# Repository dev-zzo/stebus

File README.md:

# IEEE 1000 / STEBus designs

This repository contains hardware designs based on the IEEE 1000 aka STE bus.

# Designs included

* S68k8: MC68008FN CPU board + bus arbiter
* STEP1: I/O prototyping board

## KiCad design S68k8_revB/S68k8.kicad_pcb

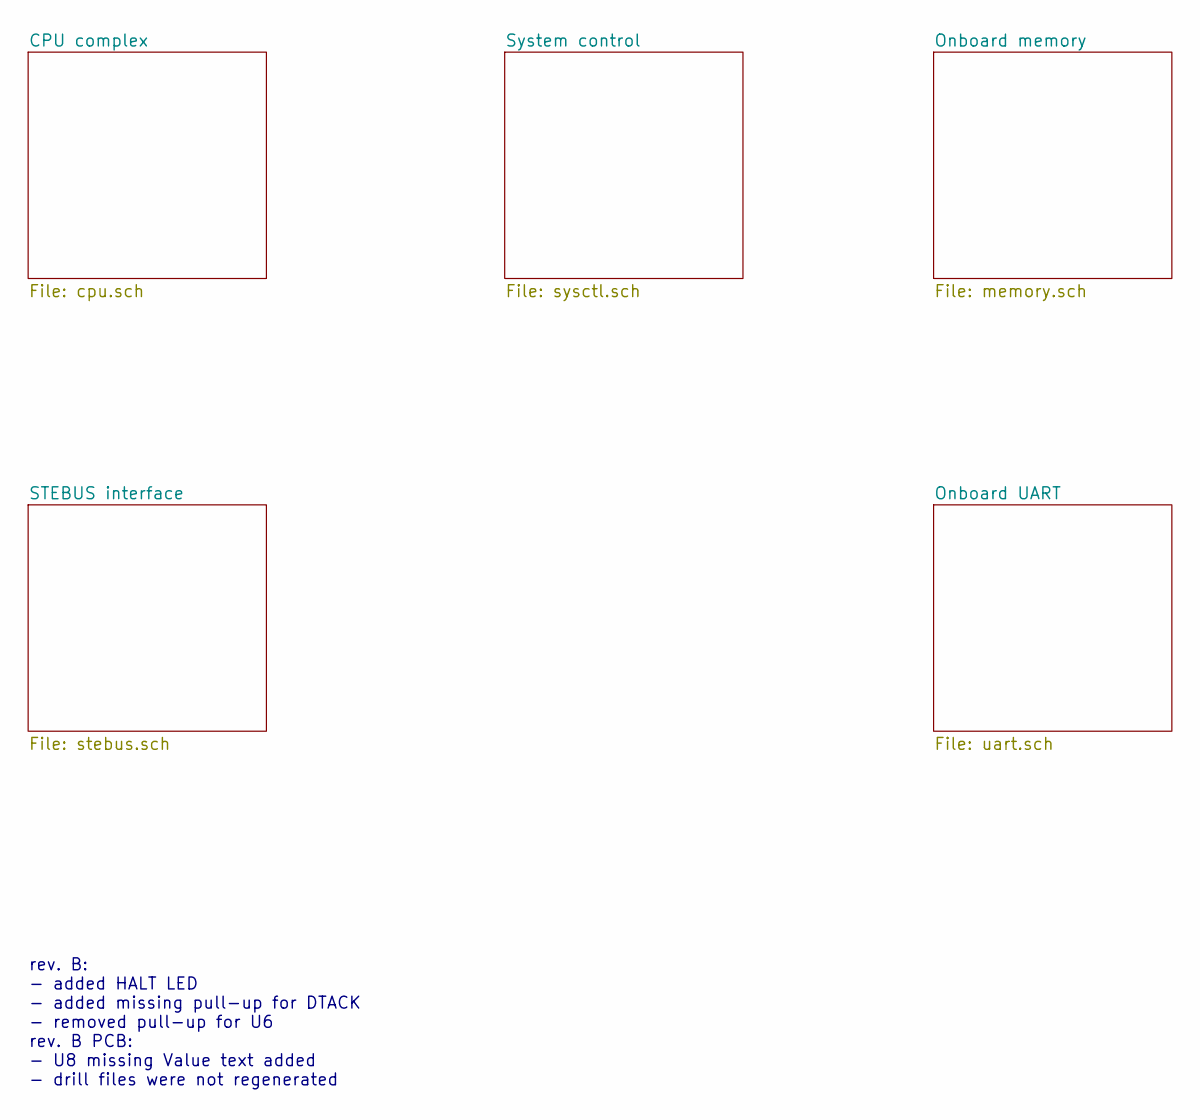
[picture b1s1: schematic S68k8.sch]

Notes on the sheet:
rev. B: - added HALT LED - added missing pull-up for DTACK - removed pull-up for U6 rev. B PCB: - U8 missing Value text added - drill files were not regenerated

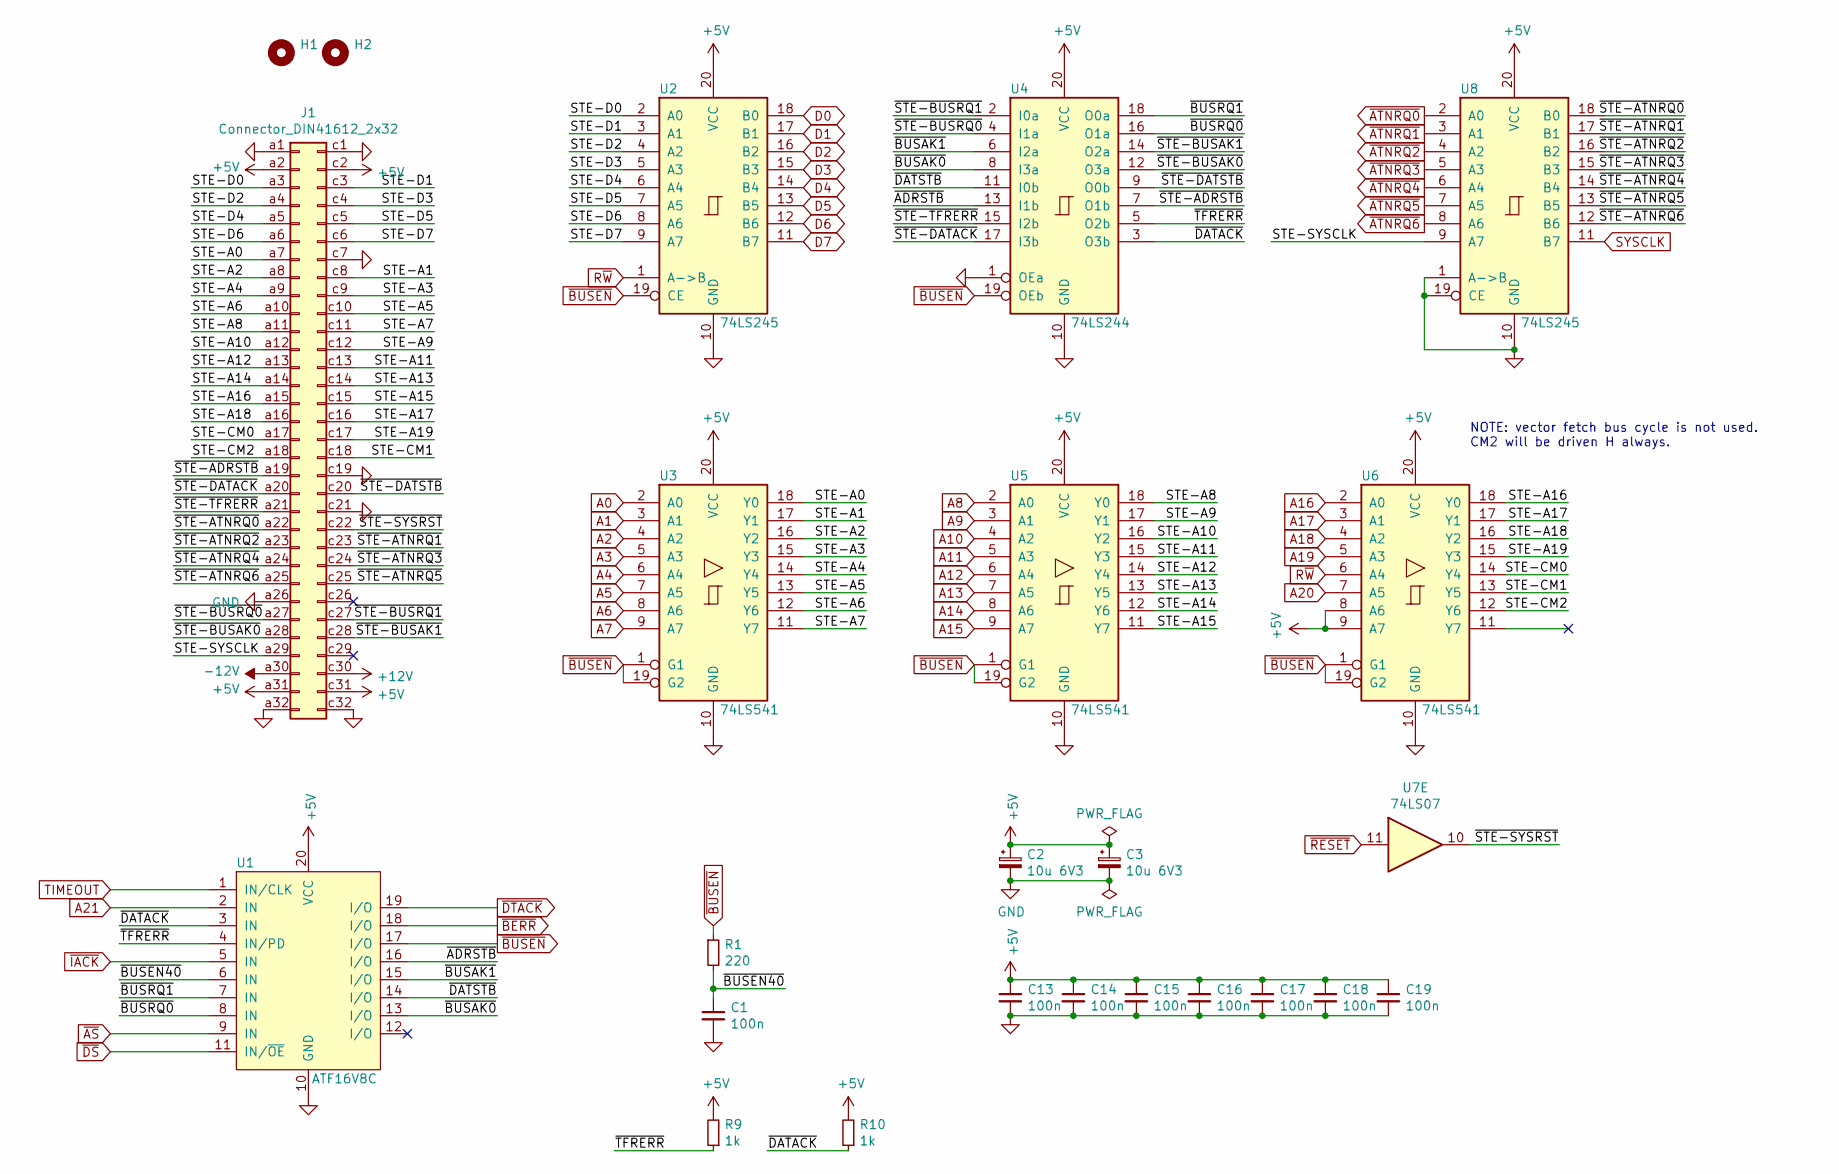
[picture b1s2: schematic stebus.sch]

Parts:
C1, C13, C14, C15, C16, C17, C18, C19: 100n; C_Rect_L7.0mm_W2.0mm_P5.00mm
C2, C3: 10u 6V3; CP_Radial_Tantal_D4.5mm_P5.00mm
H1, H2: MountingHole; MountingHole_2.7mm_M2.5
J1: Connector_DIN41612_2x32; DIN41612_C_2x32_Male_Horizontal_THT
R1: 220; R_Axial_DIN0204_L3.6mm_D1.6mm_P7.62mm_Horizontal
R9, R10: 1k; R_Axial_DIN0204_L3.6mm_D1.6mm_P7.62mm_Horizontal
U1: ATF16V8C; DIP-20_W7.62mm
U2, U8: 74LS245; DIP-20_W7.62mm
U3, U5, U6: 74LS541; DIP-20_W7.62mm
U4: 74LS244; DIP-20_W7.62mm
U7: 74LS07; DIP-14_W7.62mm

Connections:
+5V: C2.1, C3.1, C13.1, C14.1, C15.1, C16.1, C17.1, C18.1, C19.1, J1.a2, J1.a31, J1.c2, J1.c31, R9.2, R10.2, U1.20 (VCC), U2.20 (VCC), U3.20 (VCC), U4.20 (VCC), U5.20 (VCC), U6.8 (A6), U6.9 (A7), U6.20 (VCC), U8.20 (VCC); also elsewhere on the board
+12V: J1.c30; also elsewhere on the board
-12V: J1.a30; also elsewhere on the board
/STEBUS interface/STE-A0: J1.a7, U3.18 (Y0)
/STEBUS interface/STE-A1: J1.c8, U3.17 (Y1)
/STEBUS interface/STE-A2: J1.a8, U3.16 (Y2)
/STEBUS interface/STE-A3: J1.c9, U3.15 (Y3)
/STEBUS interface/STE-A4: J1.a9, U3.14 (Y4)
/STEBUS interface/STE-A5: J1.c10, U3.13 (Y5)
/STEBUS interface/STE-A6: J1.a10, U3.12 (Y6)
/STEBUS interface/STE-A7: J1.c11, U3.11 (Y7)
/STEBUS interface/STE-A8: J1.a11, U5.18 (Y0)
/STEBUS interface/STE-A9: J1.c12, U5.17 (Y1)
/STEBUS interface/STE-A10: J1.a12, U5.16 (Y2)
/STEBUS interface/STE-A11: J1.c13, U5.15 (Y3)
/STEBUS interface/STE-A12: J1.a13, U5.14 (Y4)
/STEBUS interface/STE-A13: J1.c14, U5.13 (Y5)
/STEBUS interface/STE-A14: J1.a14, U5.12 (Y6)
/STEBUS interface/STE-A15: J1.c15, U5.11 (Y7)
/STEBUS interface/STE-A16: J1.a15, U6.18 (Y0)
/STEBUS interface/STE-A17: J1.c16, U6.17 (Y1)
/STEBUS interface/STE-A18: J1.a16, U6.16 (Y2)
/STEBUS interface/STE-A19: J1.c17, U6.15 (Y3)
/STEBUS interface/STE-CM0: J1.a17, U6.14 (Y4)
/STEBUS interface/STE-CM1: J1.c18, U6.13 (Y5)
/STEBUS interface/STE-CM2: J1.a18, U6.12 (Y6)
/STEBUS interface/STE-D0: J1.a3, U2.2 (A0)
/STEBUS interface/STE-D1: J1.c3, U2.3 (A1)
/STEBUS interface/STE-D2: J1.a4, U2.4 (A2)
/STEBUS interface/STE-D3: J1.c4, U2.5 (A3)
/STEBUS interface/STE-D4: J1.a5, U2.6 (A4)
/STEBUS interface/STE-D5: J1.c5, U2.7 (A5)
/STEBUS interface/STE-D6: J1.a6, U2.8 (A6)
/STEBUS interface/STE-D7: J1.c6, U2.9 (A7)
/STEBUS interface/STE-SYSCLK: J1.a29, U8.9 (A7)
/STEBUS interface/~ADRSTB: U1.16 (I/O), U4.13 (I1b)
/STEBUS interface/~BUSAK0: U1.13 (I/O), U4.8 (I3a)
/STEBUS interface/~BUSAK1: U1.15 (I/O), U4.6 (I2a)
/STEBUS interface/~BUSEN40: C1.1, R1.2, U1.6 (IN)
/STEBUS interface/~BUSRQ0: U1.8 (IN), U4.16 (O1a)
/STEBUS interface/~BUSRQ1: U1.7 (IN), U4.18 (O0a)
/STEBUS interface/~DATACK: R10.1, U1.3 (IN), U4.3 (O3b)
/STEBUS interface/~DATSTB: U1.14 (I/O), U4.11 (I0b)
/STEBUS interface/~STE-ADRSTB: J1.a19, U4.7 (O1b)
/STEBUS interface/~STE-ATNRQ0: J1.a22, U8.18 (B0)
/STEBUS interface/~STE-ATNRQ1: J1.c23, U8.17 (B1)
/STEBUS interface/~STE-ATNRQ2: J1.a23, U8.16 (B2)
/STEBUS interface/~STE-ATNRQ3: J1.c24, U8.15 (B3)
/STEBUS interface/~STE-ATNRQ4: J1.a24, U8.14 (B4)
/STEBUS interface/~STE-ATNRQ5: J1.c25, U8.13 (B5)
/STEBUS interface/~STE-ATNRQ6: J1.a25, U8.12 (B6)
/STEBUS interface/~STE-BUSAK0: J1.a28, U4.12 (O3a)
/STEBUS interface/~STE-BUSAK1: J1.c28, U4.14 (O2a)
/STEBUS interface/~STE-BUSRQ0: J1.a27, U4.4 (I1a)
/STEBUS interface/~STE-BUSRQ1: J1.c27, U4.2 (I0a)
/STEBUS interface/~STE-DATACK: J1.a20, U4.17 (I3b)
/STEBUS interface/~STE-DATSTB: J1.c20, U4.9 (O0b)
/STEBUS interface/~STE-SYSRST: J1.c22, U7.10
/STEBUS interface/~STE-TFRERR: J1.a21, U4.15 (I2b)
/STEBUS interface/~TFRERR: R9.1, U1.4 (IN/PD), U4.5 (O2b)
A0: U3.2 (A0); also elsewhere on the board
A1: U3.3 (A1); also elsewhere on the board
A2: U3.4 (A2); also elsewhere on the board
A3: U3.5 (A3); also elsewhere on the board
A4: U3.6 (A4); also elsewhere on the board
A5: U3.7 (A5); also elsewhere on the board
A6: U3.8 (A6); also elsewhere on the board
A7: U3.9 (A7); also elsewhere on the board
A8: U5.2 (A0); also elsewhere on the board
A9: U5.3 (A1); also elsewhere on the board
A10: U5.4 (A2); also elsewhere on the board
A11: U5.5 (A3); also elsewhere on the board
A12: U5.6 (A4); also elsewhere on the board
A13: U5.7 (A5); also elsewhere on the board
A14: U5.8 (A6); also elsewhere on the board
A15: U5.9 (A7); also elsewhere on the board
A16: U6.2 (A0); also elsewhere on the board
A17: U6.3 (A1); also elsewhere on the board
A18: U6.4 (A2); also elsewhere on the board
A19: U6.5 (A3); also elsewhere on the board
A20: U6.7 (A5); also elsewhere on the board
A21: U1.2 (IN); also elsewhere on the board
D0: U2.18 (B0); also elsewhere on the board
D1: U2.17 (B1); also elsewhere on the board
D2: U2.16 (B2); also elsewhere on the board
D3: U2.15 (B3); also elsewhere on the board
D4: U2.14 (B4); also elsewhere on the board
D5: U2.13 (B5); also elsewhere on the board
D6: U2.12 (B6); also elsewhere on the board
D7: U2.11 (B7); also elsewhere on the board
GND: C1.2, C2.2, C3.2, C13.2, C14.2, C15.2, C16.2, C17.2, C18.2, C19.2, J1.a1, J1.a26, J1.a32, J1.c1, J1.c7, J1.c19, J1.c21, J1.c32, U1.10 (GND), U2.10 (GND), U3.10 (GND), U4.1 (OEa), U4.10 (GND), U5.10 (GND), U6.10 (GND), U8.1 (A->B), U8.10 (GND), U8.19 (CE); also elsewhere on the board
R~W: U2.1 (A->B), U6.6 (A4); also elsewhere on the board
SYSCLK: U8.11 (B7); also elsewhere on the board
TIMEOUT: U1.1 (IN/CLK); also elsewhere on the board
~AS: U1.9 (IN); also elsewhere on the board
~ATNRQ0: U8.2 (A0); also elsewhere on the board
~ATNRQ1: U8.3 (A1); also elsewhere on the board
~ATNRQ2: U8.4 (A2); also elsewhere on the board
~ATNRQ3: U8.5 (A3); also elsewhere on the board
~ATNRQ4: U8.6 (A4); also elsewhere on the board
~ATNRQ5: U8.7 (A5); also elsewhere on the board
~ATNRQ6: U8.8 (A6); also elsewhere on the board
~BERR: U1.18 (I/O); also elsewhere on the board
~BUSEN: R1.1, U1.17 (I/O), U2.19 (CE), U3.1 (G1), U3.19 (G2), U4.19 (OEb), U5.1 (G1), U5.19 (G2), U6.1 (G1), U6.19 (G2); also elsewhere on the board
~DS: U1.11 (IN/~OE); also elsewhere on the board
~DTACK: U1.19 (I/O); also elsewhere on the board
~IACK: U1.5 (IN); also elsewhere on the board
~RESET: U7.11; also elsewhere on the board

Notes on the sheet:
NOTE: vector fetch bus cycle is not used. CM2 will be driven H always.

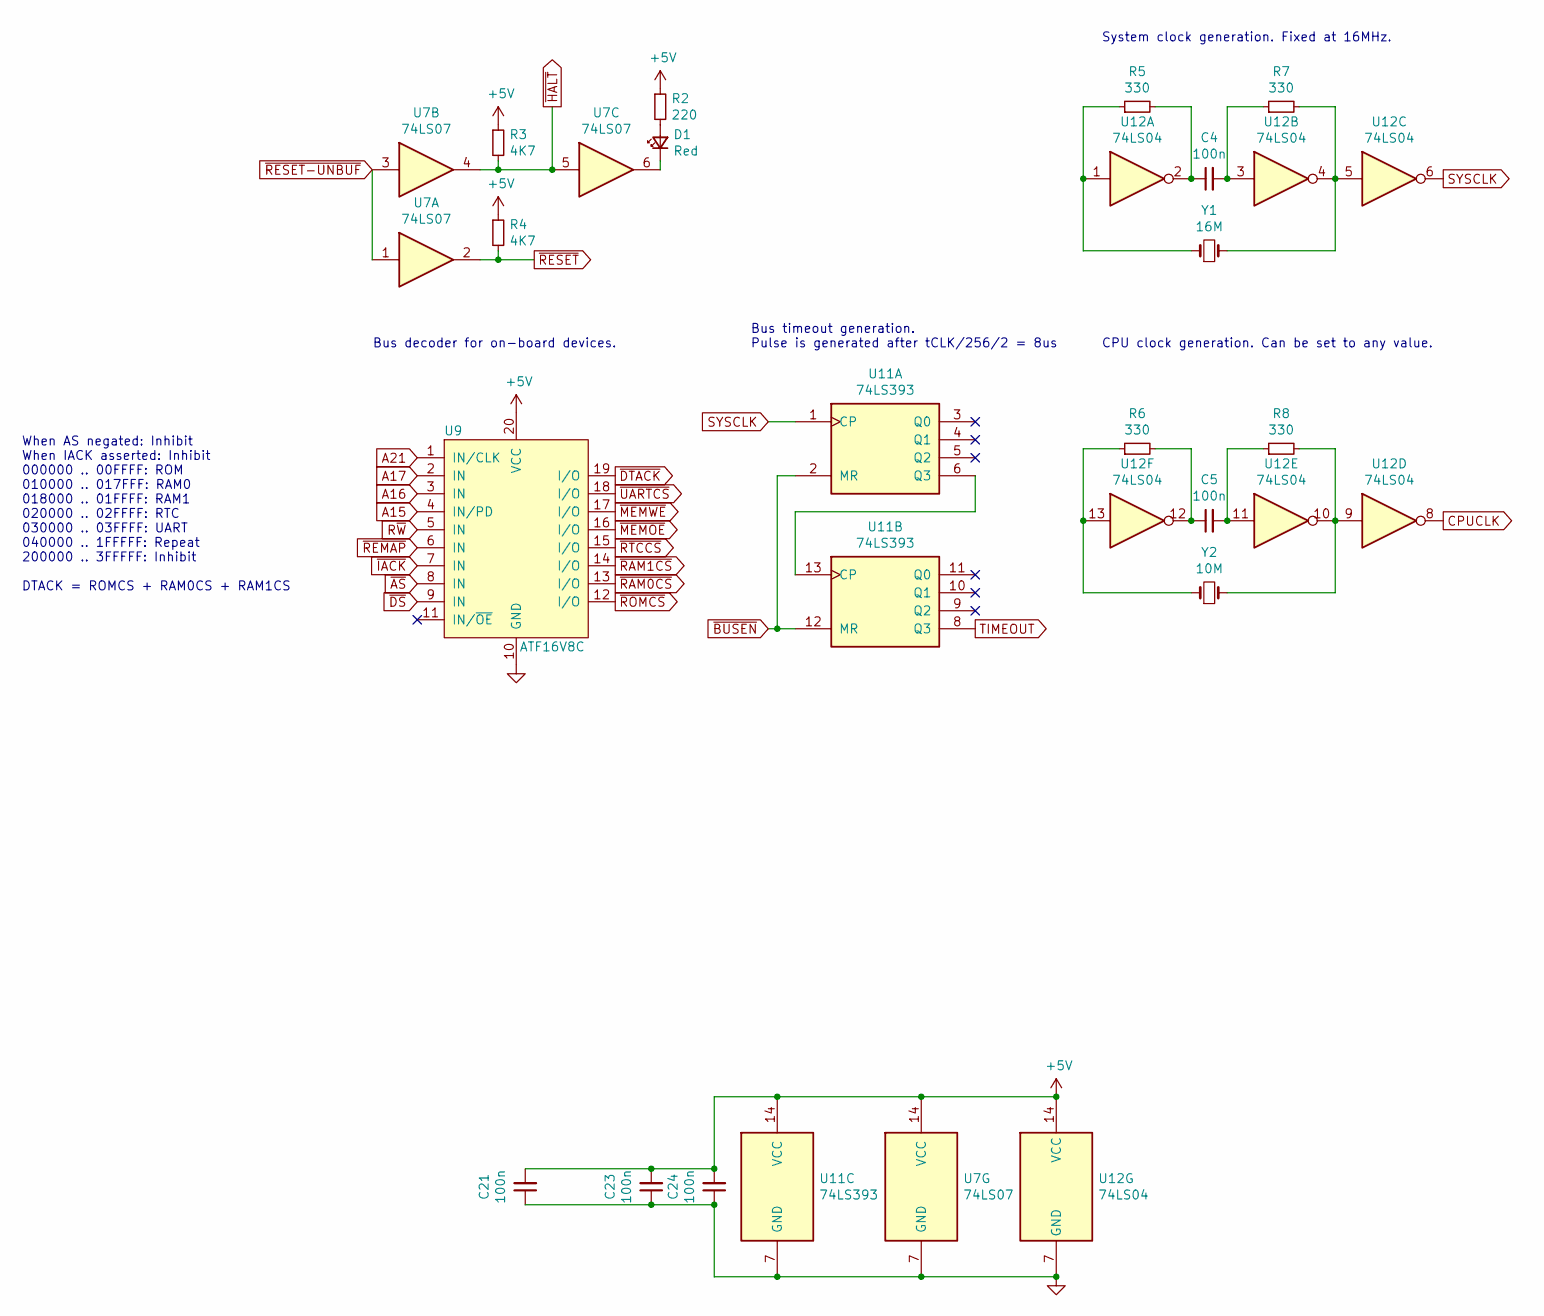
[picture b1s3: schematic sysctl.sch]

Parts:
C4, C5, C21, C23, C24: 100n; C_Rect_L7.0mm_W2.0mm_P5.00mm
D1: Red; LED_D5.0mm_Horizontal_O3.81mm_Z3.0mm
R2: 220; R_Axial_DIN0204_L3.6mm_D1.6mm_P7.62mm_Horizontal
R3, R4: 4K7; R_Axial_DIN0204_L3.6mm_D1.6mm_P7.62mm_Horizontal
R5, R6, R7, R8: 330; R_Axial_DIN0204_L3.6mm_D1.6mm_P7.62mm_Horizontal
U7: 74LS07; DIP-14_W7.62mm
U9: ATF16V8C; DIP-20_W7.62mm
U11: 74LS393; DIP-14_W7.62mm
U12: 74LS04; DIP-14_W7.62mm
Y1: 16M; Crystal_HC49-U_Vertical
Y2: 10M; Crystal_HC49-U_Vertical

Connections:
+5V: C21.2, C23.2, C24.2, R2.1, R3.1, R4.1, U7.14 (VCC), U9.20 (VCC), U11.14 (VCC), U12.14 (VCC); also elsewhere on the board
A15: U9.4 (IN/PD); also elsewhere on the board
A16: U9.3 (IN); also elsewhere on the board
A17: U9.2 (IN); also elsewhere on the board
A21: U9.1 (IN/CLK); also elsewhere on the board
CPUCLK: U12.8; also elsewhere on the board
GND: C21.1, C23.1, C24.1, U7.7 (GND), U9.10 (GND), U11.7 (GND), U12.7 (GND); also elsewhere on the board
unnamed: C4.1, R5.2, U12.2
unnamed: C4.2, R7.1, U12.3
unnamed: C5.1, R6.2, U12.12
unnamed: C5.2, R8.1, U12.11
unnamed: D1.1 (K), U7.6
unnamed: D1.2 (A), R2.2
unnamed: R5.1, U12.1, Y1.1
unnamed: R6.1, U12.13, Y2.1
unnamed: R7.2, U12.4, U12.5, Y1.2
unnamed: R8.2, U12.9, U12.10, Y2.2
unnamed: U11.6 (Q3), U11.13 (CP)
R~W: U9.5 (IN); also elsewhere on the board
SYSCLK: U11.1 (CP), U12.6; also elsewhere on the board
TIMEOUT: U11.8 (Q3); also elsewhere on the board
~AS: U9.8 (IN); also elsewhere on the board
~BUSEN: U11.2 (MR), U11.12 (MR); also elsewhere on the board
~DS: U9.9 (IN); also elsewhere on the board
~DTACK: U9.19 (I/O); also elsewhere on the board
~HALT: R3.2, U7.4, U7.5; also elsewhere on the board
~IACK: U9.7 (IN); also elsewhere on the board
~MEMOE: U9.16 (I/O); also elsewhere on the board
~MEMWE: U9.17 (I/O); also elsewhere on the board
~RAM0CS: U9.13 (I/O); also elsewhere on the board
~RAM1CS: U9.14 (I/O); also elsewhere on the board
~REMAP: U9.6 (IN); also elsewhere on the board
~RESET: R4.2, U7.2; also elsewhere on the board
~RESET-UNBUF: U7.1, U7.3; also elsewhere on the board
~ROMCS: U9.12 (I/O); also elsewhere on the board
~RTCCS: U9.15 (I/O); also elsewhere on the board
~UARTCS: U9.18 (I/O); also elsewhere on the board

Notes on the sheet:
When AS negated: Inhibit When IACK asserted: Inhibit 000000 .. 00FFFF: ROM 010000 .. 017FFF: RAM0 018000 .. 01FFFF: RAM1 020000 .. 02FFFF: RTC 030000 .. 03FFFF: UART 040000 .. 1FFFFF: Repeat 200000 .. 3FFFFF: Inhibit DTACK = ROMCS + RAM0CS + RAM1CS
Bus timeout generation. Pulse is generated after tCLK/256/2 = 8us
System clock generation. Fixed at 16MHz.
CPU clock generation. Can be set to any value.
Bus decoder for on-board devices.

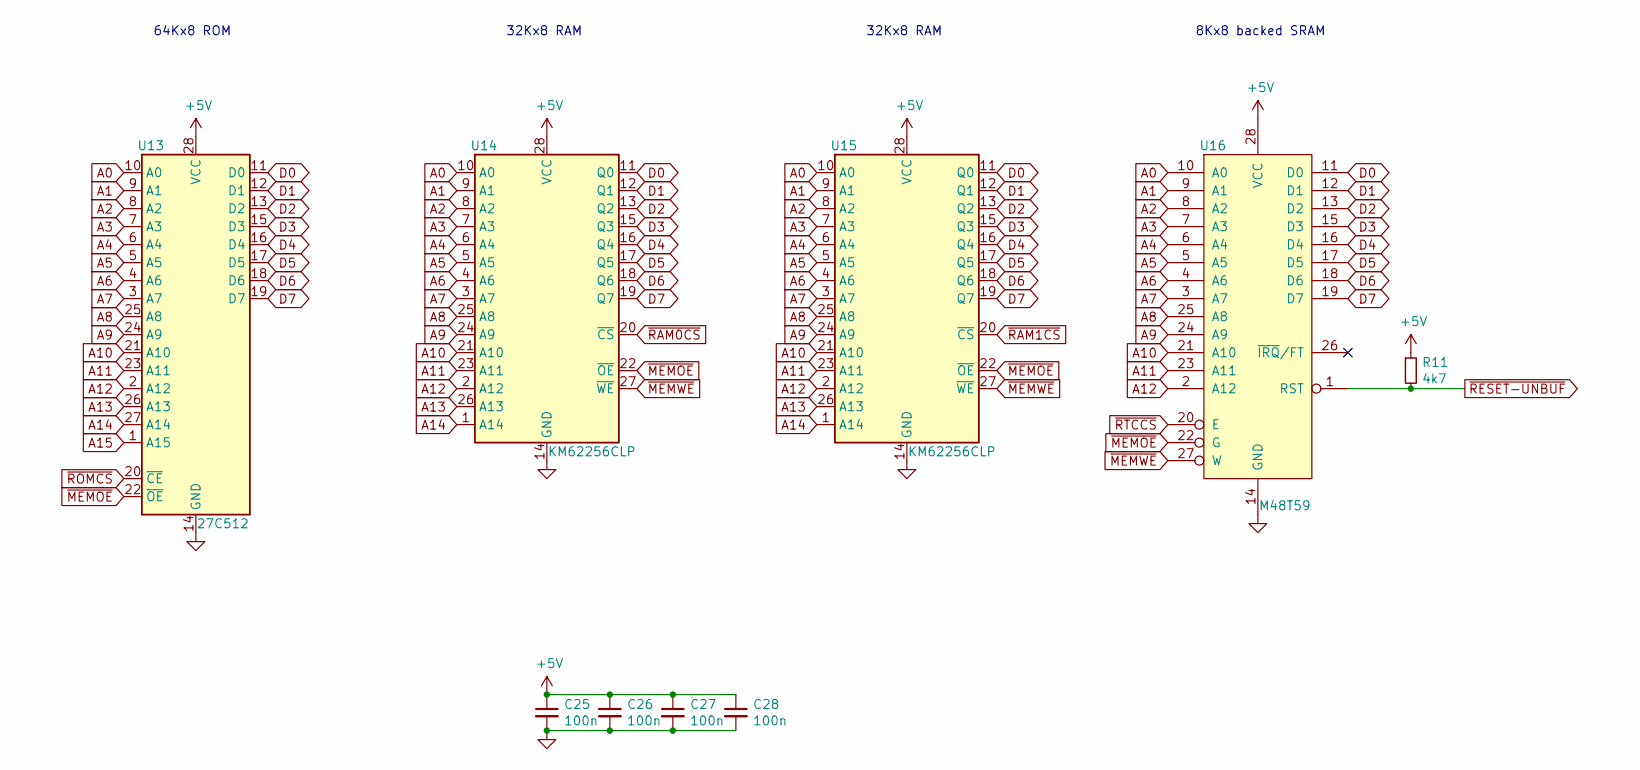
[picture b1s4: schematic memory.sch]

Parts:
C25, C26, C27, C28: 100n; C_Rect_L7.0mm_W2.0mm_P5.00mm
R11: 4k7; R_Axial_DIN0204_L3.6mm_D1.6mm_P7.62mm_Horizontal
U13: 27C512; DIP-28_W15.24mm_Socket
U14, U15: KM62256CLP; DIP-28_W15.24mm_Socket
U16: M48T59; DIP-28_W15.24mm_Socket

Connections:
+5V: C25.1, C26.1, C27.1, C28.1, R11.1, U13.28 (VCC), U14.28 (VCC), U15.28 (VCC), U16.28 (VCC); also elsewhere on the board
A0: U13.10 (A0), U14.10 (A0), U15.10 (A0), U16.10 (A0); also elsewhere on the board
A1: U13.9 (A1), U14.9 (A1), U15.9 (A1), U16.9 (A1); also elsewhere on the board
A2: U13.8 (A2), U14.8 (A2), U15.8 (A2), U16.8 (A2); also elsewhere on the board
A3: U13.7 (A3), U14.7 (A3), U15.7 (A3), U16.7 (A3); also elsewhere on the board
A4: U13.6 (A4), U14.6 (A4), U15.6 (A4), U16.6 (A4); also elsewhere on the board
A5: U13.5 (A5), U14.5 (A5), U15.5 (A5), U16.5 (A5); also elsewhere on the board
A6: U13.4 (A6), U14.4 (A6), U15.4 (A6), U16.4 (A6); also elsewhere on the board
A7: U13.3 (A7), U14.3 (A7), U15.3 (A7), U16.3 (A7); also elsewhere on the board
A8: U13.25 (A8), U14.25 (A8), U15.25 (A8), U16.25 (A8); also elsewhere on the board
A9: U13.24 (A9), U14.24 (A9), U15.24 (A9), U16.24 (A9); also elsewhere on the board
A10: U13.21 (A10), U14.21 (A10), U15.21 (A10), U16.21 (A10); also elsewhere on the board
A11: U13.23 (A11), U14.23 (A11), U15.23 (A11), U16.23 (A11); also elsewhere on the board
A12: U13.2 (A12), U14.2 (A12), U15.2 (A12), U16.2 (A12); also elsewhere on the board
A13: U13.26 (A13), U14.26 (A13), U15.26 (A13); also elsewhere on the board
A14: U13.27 (A14), U14.1 (A14), U15.1 (A14); also elsewhere on the board
A15: U13.1 (A15); also elsewhere on the board
D0: U13.11 (D0), U14.11 (Q0), U15.11 (Q0), U16.11 (D0); also elsewhere on the board
D1: U13.12 (D1), U14.12 (Q1), U15.12 (Q1), U16.12 (D1); also elsewhere on the board
D2: U13.13 (D2), U14.13 (Q2), U15.13 (Q2), U16.13 (D2); also elsewhere on the board
D3: U13.15 (D3), U14.15 (Q3), U15.15 (Q3), U16.15 (D3); also elsewhere on the board
D4: U13.16 (D4), U14.16 (Q4), U15.16 (Q4), U16.16 (D4); also elsewhere on the board
D5: U13.17 (D5), U14.17 (Q5), U15.17 (Q5), U16.17 (D5); also elsewhere on the board
D6: U13.18 (D6), U14.18 (Q6), U15.18 (Q6), U16.18 (D6); also elsewhere on the board
D7: U13.19 (D7), U14.19 (Q7), U15.19 (Q7), U16.19 (D7); also elsewhere on the board
GND: C25.2, C26.2, C27.2, C28.2, U13.14 (GND), U14.14 (GND), U15.14 (GND), U16.14 (GND); also elsewhere on the board
~MEMOE: U13.22 (~OE), U14.22 (~OE), U15.22 (~OE), U16.22 (G); also elsewhere on the board
~MEMWE: U14.27 (~WE), U15.27 (~WE), U16.27 (W); also elsewhere on the board
~RAM0CS: U14.20 (~CS); also elsewhere on the board
~RAM1CS: U15.20 (~CS); also elsewhere on the board
~RESET-UNBUF: R11.2, U16.1 (RST); also elsewhere on the board
~ROMCS: U13.20 (~CE); also elsewhere on the board
~RTCCS: U16.20 (E); also elsewhere on the board

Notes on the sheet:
64Kx8 ROM
32Kx8 RAM
8Kx8 backed SRAM

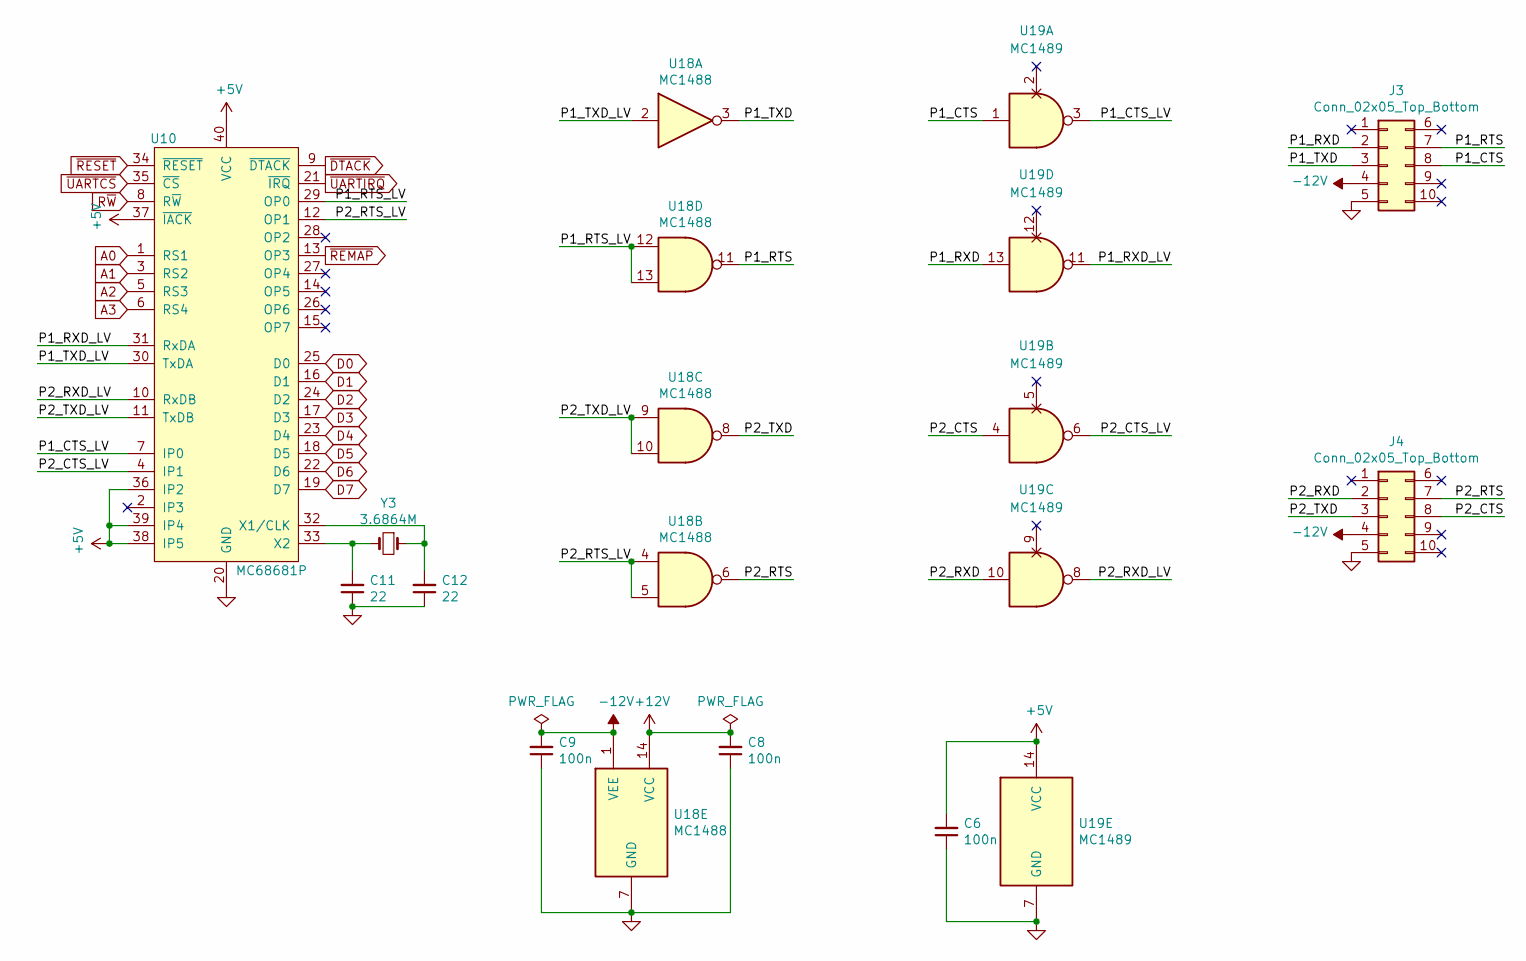
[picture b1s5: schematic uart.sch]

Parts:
C6, C8, C9: 100n; C_Rect_L7.0mm_W2.0mm_P5.00mm
C11, C12: 22; C_Rect_L7.0mm_W2.0mm_P5.00mm
J3, J4: Conn_02x05_Top_Bottom; PinSocket_2x05_P2.54mm_Vertical
U10: MC68681P; DIP-40_W15.24mm
U18: MC1488; DIP-14_W7.62mm
U19: MC1489; DIP-14_W7.62mm
Y3: 3.6864M; Crystal_HC49-U_Vertical

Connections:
+5V: C6.2, U10.36 (IP2), U10.37 (~IACK), U10.38 (IP5), U10.39 (IP4), U10.40 (VCC), U19.14 (VCC); also elsewhere on the board
+12V: C8.2, U18.14 (VCC); also elsewhere on the board
-12V: C9.2, J3.4, J4.4, U18.1 (VEE); also elsewhere on the board
/Onboard UART/P1_CTS: J3.8, U19.1
/Onboard UART/P1_CTS_LV: U10.7 (IP0), U19.3
/Onboard UART/P1_RTS: J3.7, U18.11
/Onboard UART/P1_RTS_LV: U10.29 (OP0), U18.12, U18.13
/Onboard UART/P1_RXD: J3.2, U19.13
/Onboard UART/P1_RXD_LV: U10.31 (RxDA), U19.11
/Onboard UART/P1_TXD: J3.3, U18.3
/Onboard UART/P1_TXD_LV: U10.30 (TxDA), U18.2
/Onboard UART/P2_CTS: J4.8, U19.4
/Onboard UART/P2_CTS_LV: U10.4 (IP1), U19.6
/Onboard UART/P2_RTS: J4.7, U18.6
/Onboard UART/P2_RTS_LV: U10.12 (OP1), U18.4, U18.5
/Onboard UART/P2_RXD: J4.2, U19.10
/Onboard UART/P2_RXD_LV: U10.10 (RxDB), U19.8
/Onboard UART/P2_TXD: J4.3, U18.8
/Onboard UART/P2_TXD_LV: U10.11 (TxDB), U18.9, U18.10
A0: U10.1 (RS1); also elsewhere on the board
A1: U10.3 (RS2); also elsewhere on the board
A2: U10.5 (RS3); also elsewhere on the board
A3: U10.6 (RS4); also elsewhere on the board
D0: U10.25 (D0); also elsewhere on the board
D1: U10.16 (D1); also elsewhere on the board
D2: U10.24 (D2); also elsewhere on the board
D3: U10.17 (D3); also elsewhere on the board
D4: U10.23 (D4); also elsewhere on the board
D5: U10.18 (D5); also elsewhere on the board
D6: U10.22 (D6); also elsewhere on the board
D7: U10.19 (D7); also elsewhere on the board
GND: C6.1, C8.1, C9.1, C11.1, C12.1, J3.5, J4.5, U10.20 (GND), U18.7 (GND), U19.7 (GND); also elsewhere on the board
unnamed: C11.2, U10.33 (X2), Y3.2
unnamed: C12.2, U10.32 (X1/CLK), Y3.1
R~W: U10.8 (R~W); also elsewhere on the board
~DTACK: U10.9 (~DTACK); also elsewhere on the board
~REMAP: U10.13 (OP3); also elsewhere on the board
~RESET: U10.34 (~RESET); also elsewhere on the board
~UARTCS: U10.35 (~CS); also elsewhere on the board
~UARTIRQ: U10.21 (~IRQ); also elsewhere on the board

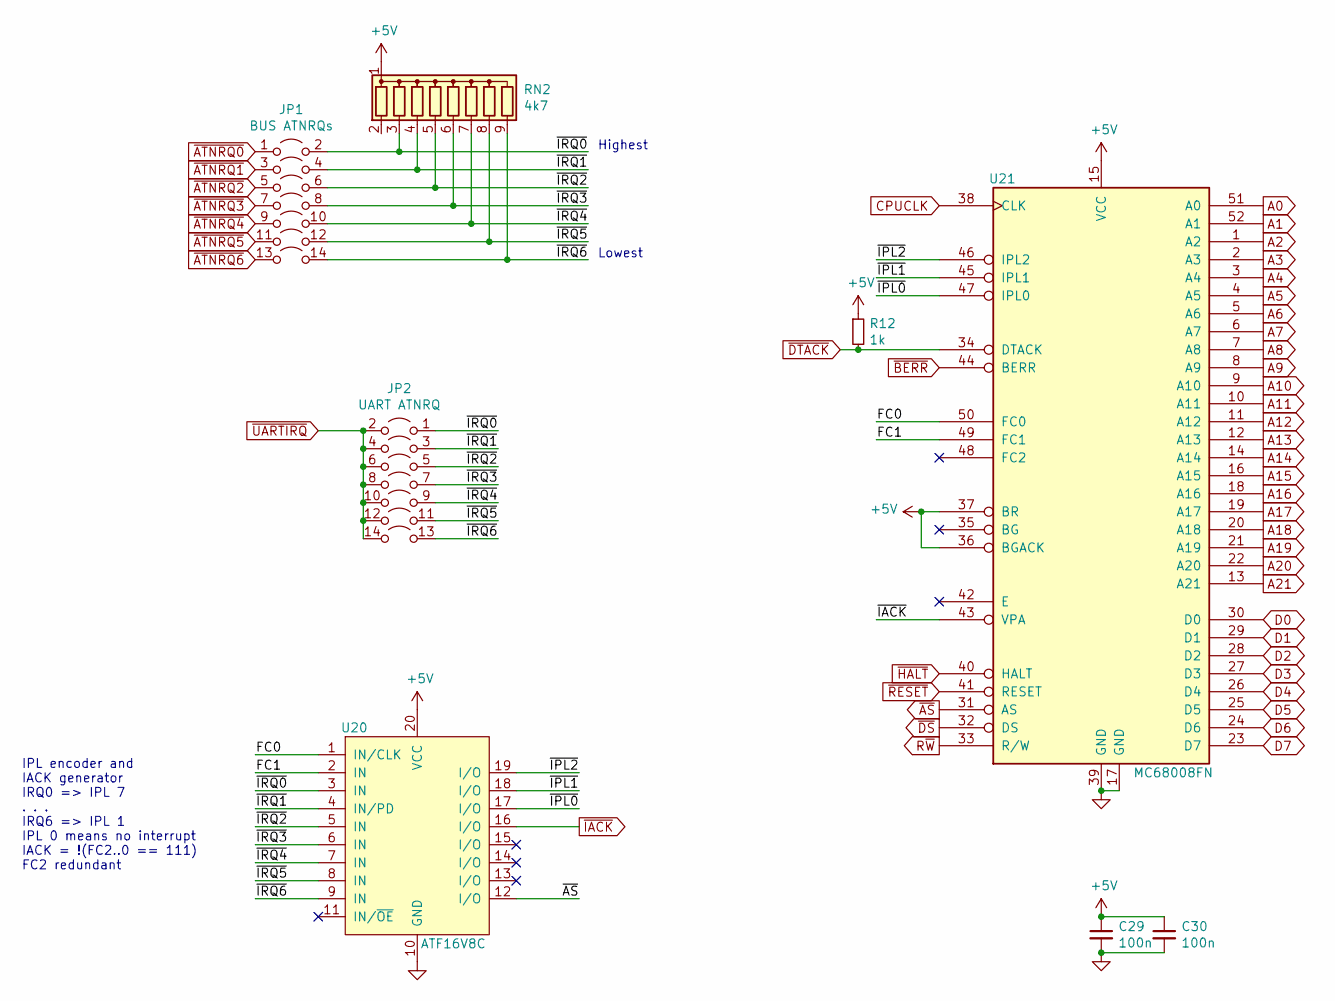
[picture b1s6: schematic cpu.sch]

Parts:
C29, C30: 100n; C_Rect_L7.0mm_W2.0mm_P5.00mm
JP1: BUS ATNRQs; PinSocket_2x07_P2.54mm_Vertical
JP2: UART ATNRQ; PinSocket_2x07_P2.54mm_Vertical
R12: 1k; R_Axial_DIN0204_L3.6mm_D1.6mm_P7.62mm_Horizontal
RN2: 4k7; R_Array_SIP9
U20: ATF16V8C; DIP-20_W7.62mm
U21: MC68008FN; PLCC-52_THT-Socket

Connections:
+5V: C29.1, C30.1, R12.1, RN2.1 (common), U20.20 (VCC), U21.15 (VCC), U21.36 (BGACK), U21.37 (BR); also elsewhere on the board
/CPU complex/FC0: U20.1 (IN/CLK), U21.50 (FC0)
/CPU complex/FC1: U20.2 (IN), U21.49 (FC1)
/CPU complex/~IPL0: U20.17 (I/O), U21.47 (IPL0)
/CPU complex/~IPL1: U20.18 (I/O), U21.45 (IPL1)
/CPU complex/~IPL2: U20.19 (I/O), U21.46 (IPL2)
/CPU complex/~IRQ0: JP1.2 (B), JP2.1 (A), RN2.3 (R2), U20.3 (IN)
/CPU complex/~IRQ1: JP1.4 (B), JP2.3 (A), RN2.4 (R3), U20.4 (IN/PD)
/CPU complex/~IRQ2: JP1.6 (B), JP2.5 (A), RN2.5 (R4), U20.5 (IN)
/CPU complex/~IRQ3: JP1.8 (B), JP2.7 (A), RN2.6 (R5), U20.6 (IN)
/CPU complex/~IRQ4: JP1.10 (B), JP2.9 (A), RN2.7 (R6), U20.7 (IN)
/CPU complex/~IRQ5: JP1.12 (B), JP2.11 (A), RN2.8 (R7), U20.8 (IN)
/CPU complex/~IRQ6: JP1.14 (B), JP2.13 (A), RN2.9 (R8), U20.9 (IN)
A0: U21.51 (A0); also elsewhere on the board
A1: U21.52 (A1); also elsewhere on the board
A2: U21.1 (A2); also elsewhere on the board
A3: U21.2 (A3); also elsewhere on the board
A4: U21.3 (A4); also elsewhere on the board
A5: U21.4 (A5); also elsewhere on the board
A6: U21.5 (A6); also elsewhere on the board
A7: U21.6 (A7); also elsewhere on the board
A8: U21.7 (A8); also elsewhere on the board
A9: U21.8 (A9); also elsewhere on the board
A10: U21.9 (A10); also elsewhere on the board
A11: U21.10 (A11); also elsewhere on the board
A12: U21.11 (A12); also elsewhere on the board
A13: U21.12 (A13); also elsewhere on the board
A14: U21.14 (A14); also elsewhere on the board
A15: U21.16 (A15); also elsewhere on the board
A16: U21.18 (A16); also elsewhere on the board
A17: U21.19 (A17); also elsewhere on the board
A18: U21.20 (A18); also elsewhere on the board
A19: U21.21 (A19); also elsewhere on the board
A20: U21.22 (A20); also elsewhere on the board
A21: U21.13 (A21); also elsewhere on the board
CPUCLK: U21.38 (CLK); also elsewhere on the board
D0: U21.30 (D0); also elsewhere on the board
D1: U21.29 (D1); also elsewhere on the board
D2: U21.28 (D2); also elsewhere on the board
D3: U21.27 (D3); also elsewhere on the board
D4: U21.26 (D4); also elsewhere on the board
D5: U21.25 (D5); also elsewhere on the board
D6: U21.24 (D6); also elsewhere on the board
D7: U21.23 (D7); also elsewhere on the board
GND: C29.2, C30.2, U20.10 (GND), U21.17 (GND), U21.39 (GND); also elsewhere on the board
R~W: U21.33 (R/W); also elsewhere on the board
~AS: U20.12 (I/O), U21.31 (AS); also elsewhere on the board
~ATNRQ0: JP1.1 (A); also elsewhere on the board
~ATNRQ1: JP1.3 (A); also elsewhere on the board
~ATNRQ2: JP1.5 (A); also elsewhere on the board
~ATNRQ3: JP1.7 (A); also elsewhere on the board
~ATNRQ4: JP1.9 (A); also elsewhere on the board
~ATNRQ5: JP1.11 (A); also elsewhere on the board
~ATNRQ6: JP1.13 (A); also elsewhere on the board
~BERR: U21.44 (BERR); also elsewhere on the board
~DS: U21.32 (DS); also elsewhere on the board
~DTACK: R12.2, U21.34 (DTACK); also elsewhere on the board
~HALT: U21.40 (HALT); also elsewhere on the board
~IACK: U20.16 (I/O), U21.43 (VPA); also elsewhere on the board
~RESET: U21.41 (RESET); also elsewhere on the board
~UARTIRQ: JP2.2 (B), JP2.4 (B), JP2.6 (B), JP2.8 (B), JP2.10 (B), JP2.12 (B), JP2.14 (B); also elsewhere on the board

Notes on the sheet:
IPL encoder and IACK generator IRQ0 => IPL 7 . . . IRQ6 => IPL 1 IPL 0 means no interrupt IACK = !(FC2..0 == 111) FC2 redundant
Highest
Lowest

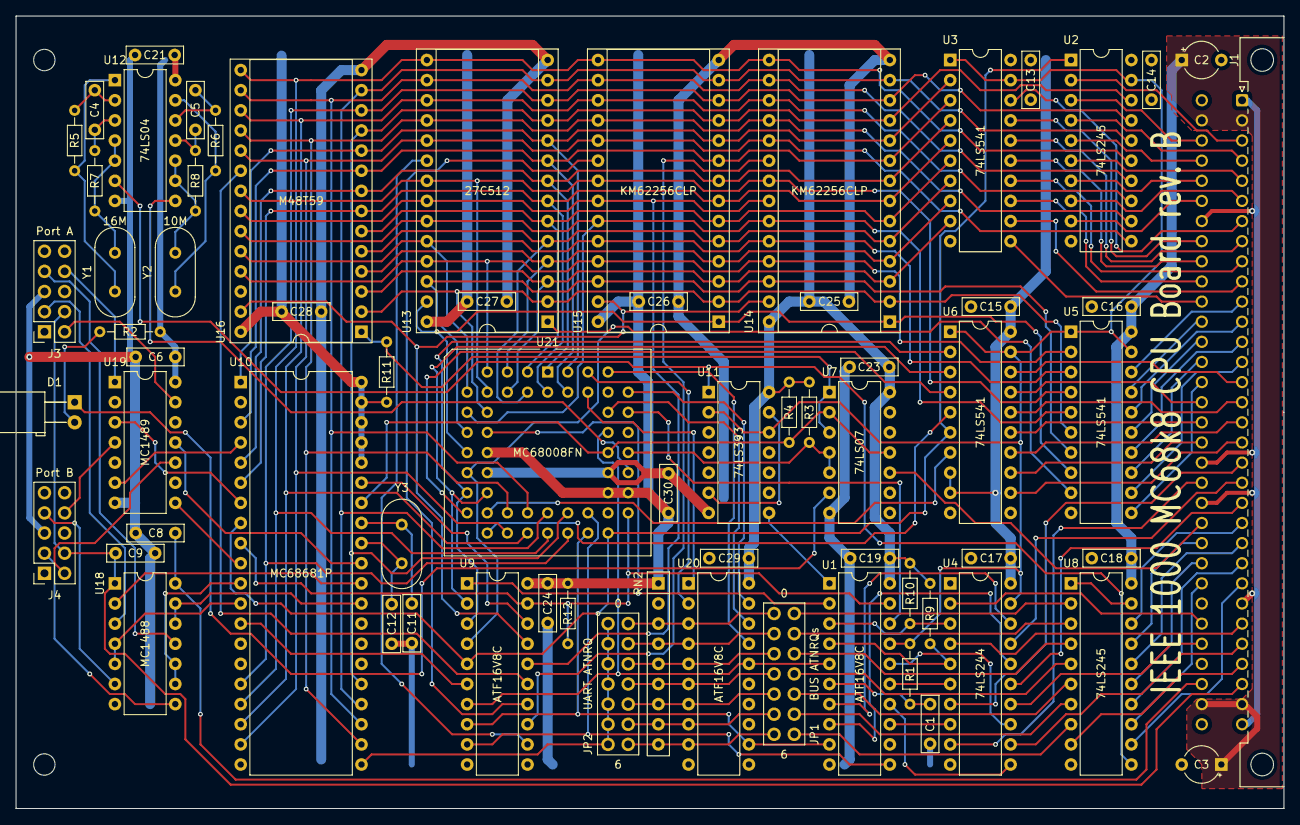
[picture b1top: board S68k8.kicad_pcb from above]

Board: 2 copper layers, 160.0 x 100.0 mm, 70 parts (0 on the bottom side), 161 nets.
